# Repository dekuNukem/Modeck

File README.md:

Modeck is a physical control panel for Twitch broadcasters.

## Features

- Dedicated controls for sub mode, slow mode, and playing commercials
- No more interrupting stream to type commands into chat
- 6 user customizable buttons/switches, can be either set to send chat messages or act like keyboard hot keys
- Backlit pushbuttons with adjustable brightness, indicator lights on toggle switches
- Cross platform (Windows, OS X, Linux)
- No driver needed on all platforms

## Video Demonstrations 

Please go to [this album](http://imgur.com/a/pS2iP) to see Modeck in action.

## Questions?

Feel free to contact me here, or via:

Email: dekuNukem@gmail.com

Twitter: @dekuNukem_tp3ds

Reddit: /u/dekuNukem

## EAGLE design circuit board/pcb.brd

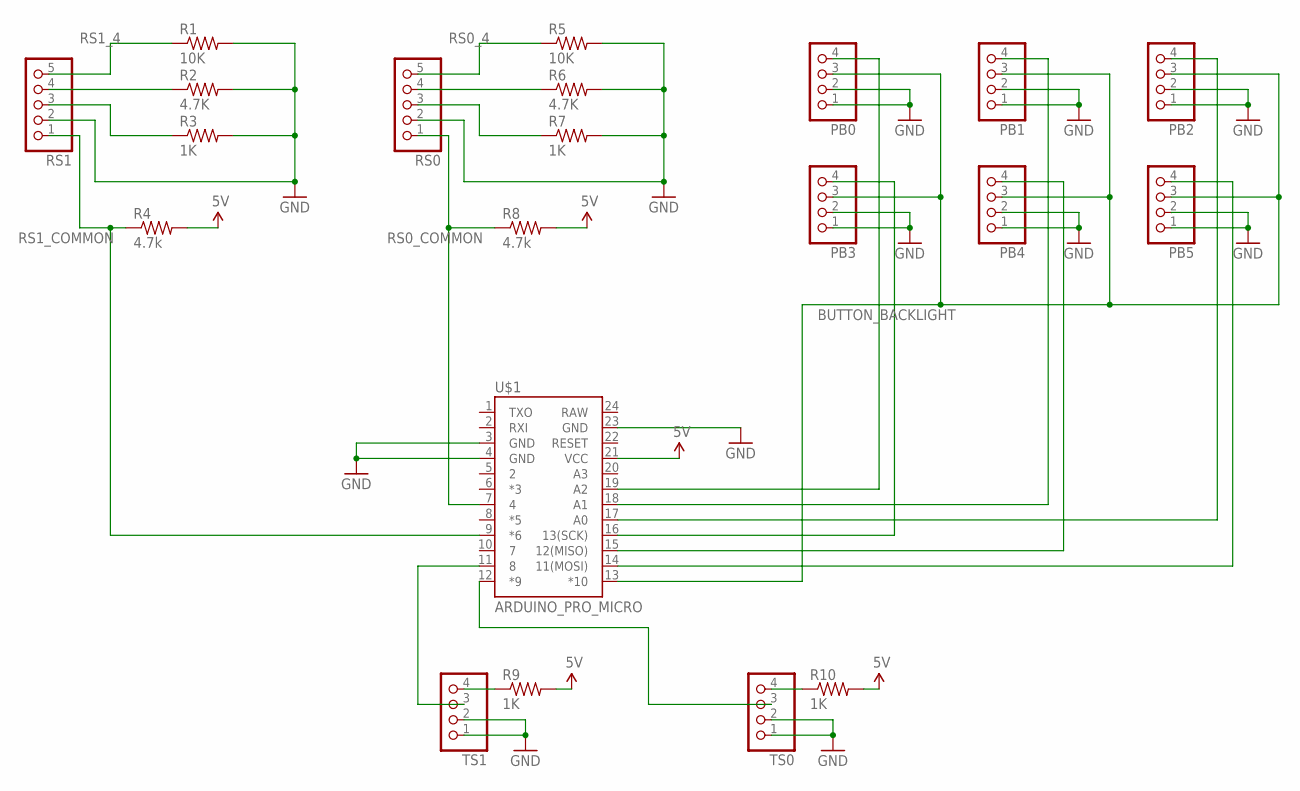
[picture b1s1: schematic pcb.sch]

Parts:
PB0, PB1, PB2, PB3, PB4, PB5: PINHD-1X4; 1X04
R1, R5: 10K; AXIAL-0.3EZ
R2, R6: 4.7K; AXIAL-0.3EZ
R3, R7, R9, R10: 1K; AXIAL-0.3EZ
R4, R8: 4.7k; AXIAL-0.3EZ
RS0, RS1: PINHD-1X5; 1X05
TS0, TS1: PINHD-1X4; 1X04
U$1: ARDUINO_PRO_MICRO

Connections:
5V: R4.P$2 (2), R8.P$2 (2), R9.P$2 (2), R10.P$2 (2), U$1.21 (VCC)
BUTTON_BACKLIGHT: PB0.3, PB1.3, PB2.3, PB3.3, PB4.3, PB5.3, U$1.13 (*10)
GND: PB0.1, PB0.2, PB1.1, PB1.2, PB2.1, PB2.2, PB3.1, PB3.2, PB4.1, PB4.2, PB5.1, PB5.2, R1.P$2 (2), R2.P$2 (2), R3.P$2 (2), R5.P$2 (2), R6.P$2 (2), R7.P$2 (2), RS0.2, RS1.2, TS0.1, TS0.2, TS1.1, TS1.2, U$1.3 (GND), U$1.4 (GND), U$1.23 (GND)
unnamed: R9.P$1 (1), TS1.4
unnamed: R10.P$1 (1), TS0.4
unnamed: TS1.3, U$1.11 (8)
unnamed: PB5.4, U$1.14 (11(MOSI))
unnamed: PB4.4, U$1.15 (12(MISO))
unnamed: PB3.4, U$1.16 (13(SCK))
unnamed: PB2.4, U$1.17 (A0)
unnamed: PB1.4, U$1.18 (A1)
unnamed: PB0.4, U$1.19 (A2)
unnamed: TS0.3, U$1.12 (*9)
RS0_2: R7.P$1 (1), RS0.3
RS0_3: R6.P$1 (1), RS0.4
RS0_4: R5.P$1 (1), RS0.5
RS0_COMMON: R8.P$1 (1), RS0.1, U$1.7 (4)
RS1_2: R3.P$1 (1), RS1.3
RS1_3: R2.P$1 (1), RS1.4
RS1_4: R1.P$1 (1), RS1.5
RS1_COMMON: R4.P$1 (1), RS1.1, U$1.9 (*6)

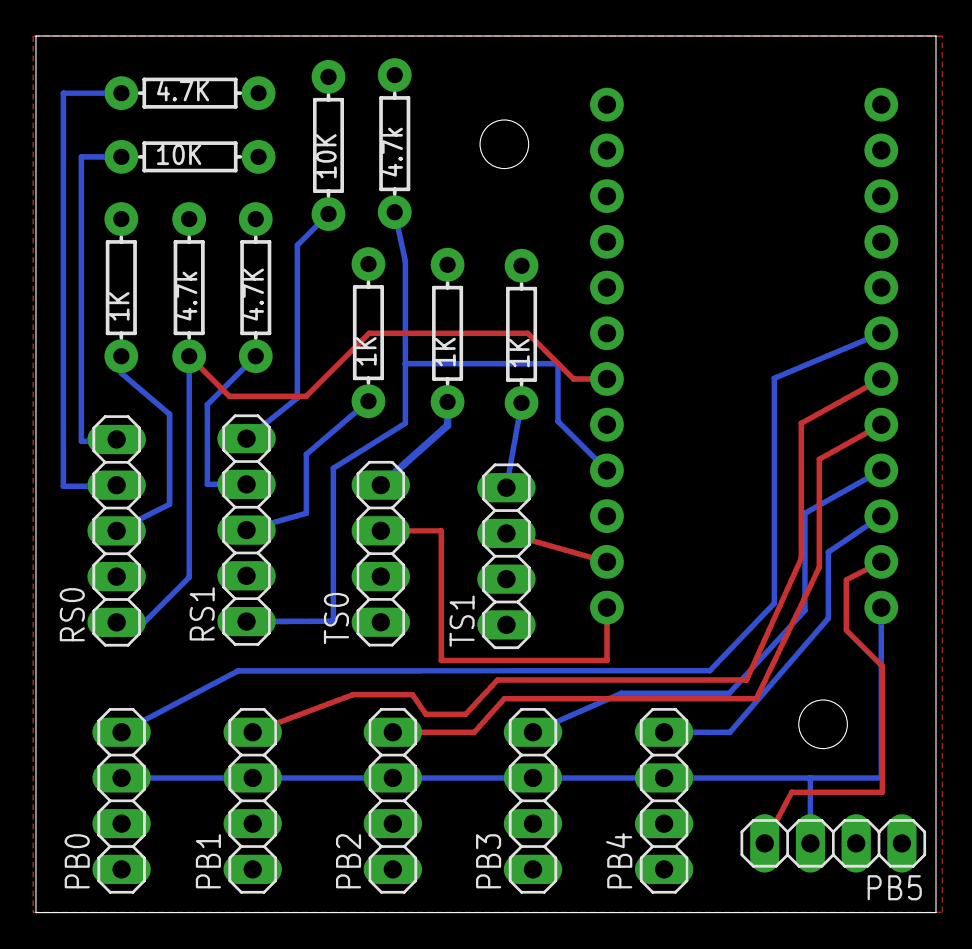
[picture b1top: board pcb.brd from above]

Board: 2 copper layers, 50.0 x 48.7 mm, 21 parts (0 on the bottom side), 21 nets.

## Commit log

2015-12-07 writing README

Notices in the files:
parts and their libraries:
SparkFun-Resistors: Licensing: Creative Commons ShareAlike 4.0 International - https://creativecommons.org/licenses/by-sa/4.0
